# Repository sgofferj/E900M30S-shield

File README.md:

# Breakout board for eByte E22 SPI modules with CM4 footprint

License: CC-BY-SA 4.0

The main purpose of this board is easy connection of an eByte E22 SPI module to a CM4 baseboard but it also works great as a general breakout board for experiments with one of the E22-xxxMyyS modules.

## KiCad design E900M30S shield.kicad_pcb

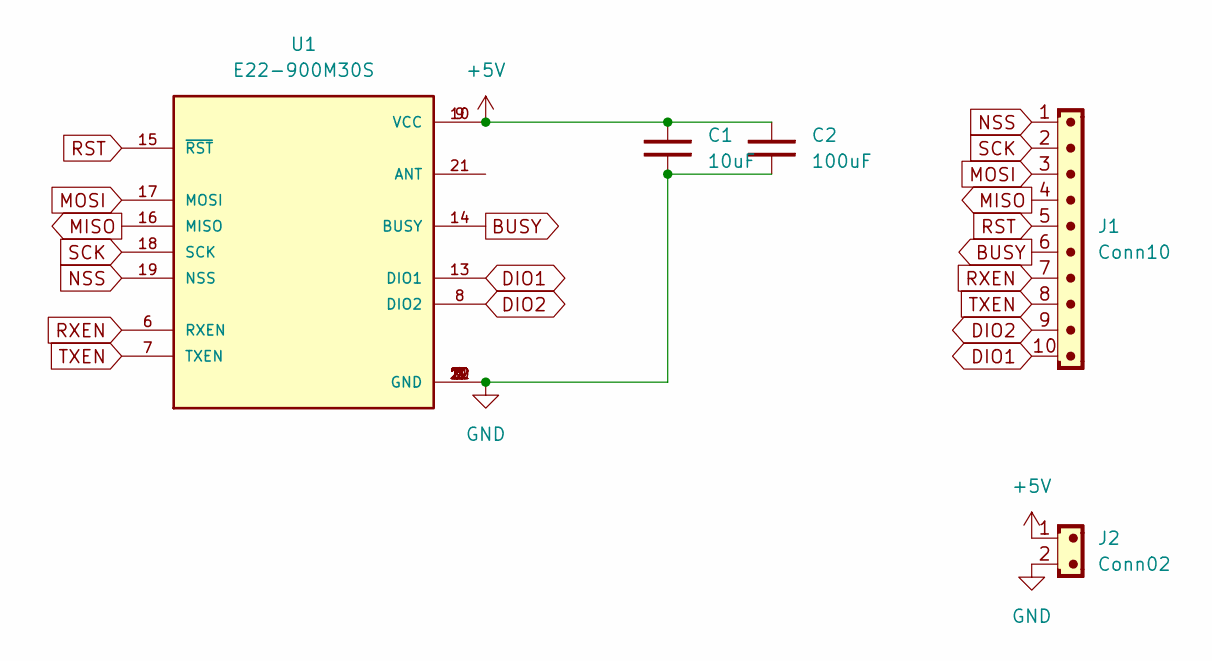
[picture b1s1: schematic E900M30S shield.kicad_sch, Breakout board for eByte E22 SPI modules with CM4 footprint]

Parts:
C1: 10uF; C_1210_3225Metric
C2: 100uF; C_1210_3225Metric
J1: Conn10; PinHeader_1x10_P2.54mm_Vertical
J2: Conn02; PinHeader_1x02_P2.54mm_Vertical
U1: E22-900M30S; XCVR_E22-900M30S; PARTREV 1.2

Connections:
+5V: C1.1, C2.1, J2.1, U1.9 (VCC), U1.10 (VCC)
BUSY: J1.6, U1.14 (BUSY)
DIO1: J1.10, U1.13 (DIO1)
DIO2: J1.9, U1.8 (DIO2)
GND: C1.2, C2.2, J2.2, U1.1 (GND), U1.2 (GND), U1.3 (GND), U1.4 (GND), U1.5 (GND), U1.11 (GND), U1.12 (GND), U1.20 (GND), U1.22 (GND)
MISO: J1.4, U1.16 (MISO)
MOSI: J1.3, U1.17 (MOSI)
NSS: J1.1, U1.19 (NSS)
RST: J1.5, U1.15 (~RST)
RXEN: J1.7, U1.6 (RXEN)
SCK: J1.2, U1.18 (SCK)
TXEN: J1.8, U1.7 (TXEN)

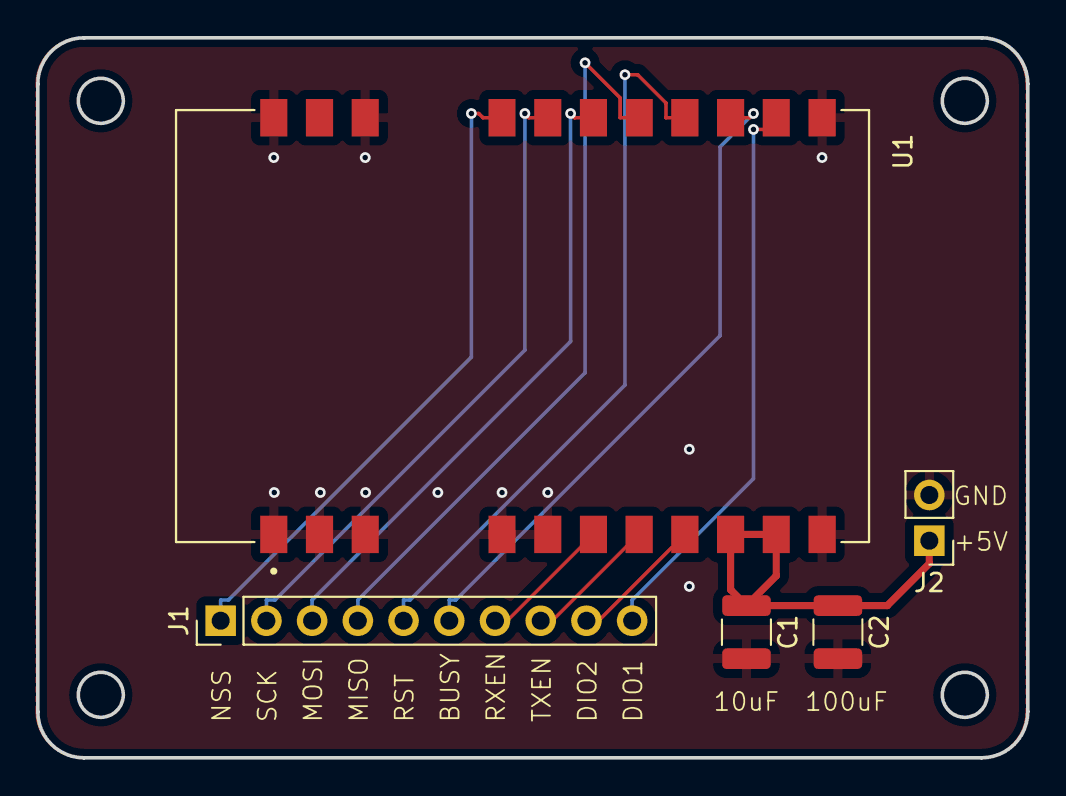
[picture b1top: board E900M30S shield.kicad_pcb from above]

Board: 2 copper layers, 55.0 x 40.0 mm, 5 parts (0 on the bottom side), 12 nets.

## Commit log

2025-02-13 Remove autosave files from git
2025-02-13 Renaming everything correctly
2025-02-13 Update cap values
2025-02-14 Rearrange decoupling caps Front side ground plane Double width power traces
2025-02-14 Final touches
2025-02-15 Add Gerbers
2025-02-18 Redesign to keep tracks away from under the module as per datasheet
2025-02-18 Redesign to keep tracks off from under the module
2025-02-26 Update gerbers
